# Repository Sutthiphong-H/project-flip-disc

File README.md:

# FlipDisc Project

FlipDisc Project was made for education of Project.
Chadsadakorn Piriyasiriphan
Jadesalit Suriyanimitsuk
Sutthiphong Hongkham

A webcam feed is segmented with RVM (Robust Video Matting; U2NET optional), each silhouette's distance is estimated from
its height, and everyone beyond `FLIPDISC_MAX_DISTANCE` is dropped. What's left is
reduced to an 80x45 black-and-white matrix and streamed to the React frontend over
Socket.IO. With nobody in range the backend loops an idle video instead.

## Layout

```
backend/
├── assets/            idle video clips
├── models/            model weights (not committed)
├── requirements.txt
├── src/
│   ├── app.py         entry point
│   ├── settings.py    every tunable, overridable by environment variable
│   ├── pipeline.py    capture -> segment -> publish loop
│   ├── frame_rate.py  rolling FPS meter
│   ├── sources/       webcam capture, idle video playback
│   ├── vision/        RVM + U2NET models, segmentation worker
│   └── server/        Flask + Socket.IO server and publisher
└── tools/camtest.py   preview a camera to find its index
flip-disc_frontend/    React client
arduino/               ESP32 sketches
```

## Installation

The RTX 50-series needs a CUDA 12.8 build of torch, so install torch first:

```bash
cd backend
pip install torch torchvision --index-url https://download.pytorch.org/whl/cu128
pip install -r requirements.txt
```

On a machine without an NVIDIA GPU, install the much smaller CPU build instead
(`--index-url https://download.pytorch.org/whl/cpu`). The backend runs on the CPU
by itself when there is no GPU, or the GPU fails a test run. That includes cards
older than the RTX 20-series, which the cu128 build has no kernels for. It also
falls back when the GPU can't load the model.

| Device | Model input | Per frame | fps with this webcam |
| ------ | ----------- | --------- | -------------------- |
| RTX 5060 (CUDA graph) | 1280x720 | ~8.5 ms | 20 (the camera's limit) |
| CPU, 6 threads | 640x360 | ~47 ms | ~17 |

The header of the page shows `GPU` or `CPU` (in amber) for the one in use.

Put the weights in `backend/models/`:

- `rvm_mobilenetv3.pth` -- the default model ([download](https://github.com/PeterL1n/RobustVideoMatting/releases/download/v1.0.0/rvm_mobilenetv3.pth))
- `u2net_human_seg.pth` -- only needed for `FLIPDISC_MODEL=u2net` ([download](https://drive.usercontent.google.com/download?id=1m_Kgs91b21gayc2XLW0ou8yugAIadWVP&export=download&authuser=0&confirm=t))

Put the idle clip at `backend/assets/video.mp4` (not in git -- it's 90 MB).

RVM's code in `backend/src/vision/rvm/` is vendored from [RobustVideoMatting](https://github.com/PeterL1n/RobustVideoMatting) and is GPL-3.0.

```bash
cd flip-disc_frontend
npm install
```

## Running

Build the frontend once and the backend serves it -- open http://localhost:5000:

```bash
cd flip-disc_frontend
npm run build            # -> flip-disc_frontend/dist (FLIPDISC_FRONTEND_DIST to move it)
cd ../backend
python src/app.py        # Flask + Socket.IO + the built page, all on port 5000
```

While working on the frontend, use Vite's dev server instead (http://localhost:5173,
talks to the backend on port 5000):

```bash
cd flip-disc_frontend
npm run dev
```

### Running unattended

`backend/run-backend.bat` runs the backend and restarts it whenever it exits with an
error. The backend exits with code 1 by itself when something breaks and won't
recover in place: the pipeline thread dies (a model that won't load, a CUDA context
broken by a GPU driver reset), segmentation hangs, or no frame goes out for
`FLIPDISC_STALL_SECONDS`. Frames go out in every mode (the idle clip plays even
without a camera), so a gap in them always means the backend is stuck. Ctrl+C exits with 0 and ends
the script too.

To start it with Windows, create a Task Scheduler task with the trigger **At log on**
and the action `backend\run-backend.bat`. Use log on rather than a Windows service:
services run outside the desktop session, and webcam access from there is unreliable. On the display machine, also turn off
sleep and USB selective suspend (Power Options → USB settings), or the webcam
can be powered down.

- `GET /status` returns 503 with `"status": "stalled"` once frames stop, for an
  external health check. Before the first frame the status is `"starting"`.
- The page shows *No frames from the backend* when it is connected but nothing has
  arrived for 3 s, and *Disconnected* once the backend has exited.
- If WebGL loses its context (a GPU reset, a driver update), the flip-disc view
  rebuilds itself. You don't need to reload.

Cameras are managed from the camera icon at the top right of the page: pick the
camera in use from the dropdown, and add, edit or delete cameras.

- **Webcam**: *Scan* shows the webcams plugged into the backend machine (with a
  thumbnail each); pick one, give it a name and a resolution.
- **IP camera**: name, IP, port, username, password, channel, main/sub stream,
  brand and resolution. The RTSP URL is built from those: Dahua
  `.../cam/realmonitor?channel=1&subtype=0` or Hikvision `.../Streaming/Channels/101`.
- *Test* grabs one frame and shows it. The backend only switches to a camera that
  delivers a picture, otherwise the current one keeps running.

The list lives in `backend/cameras.json` -- not committed, since it holds the IP
cameras' passwords, which the page never gets back (a blank password when editing
keeps the saved one). Without that file the backend starts with webcam `FLIPDISC_CAMERA`.

The page has three views: **Flip-disc** (the simulated display), **Mask** (the raw
80x45 matrix) and **Camera** (the webcam with the silhouette highlighted and a
distance box per person, streamed from `/debug.mjpg` only while it's open).

## Environment variables

| Variable                   | Default      | Meaning                                  |
| -------------------------- | ------------ | ---------------------------------------- |
| `FLIPDISC_CAMERA`          | `0`          | First webcam, until `cameras.json` exists |
| `FLIPDISC_PORT`            | `5000`       | Socket.IO / HTTP port                    |
| `FLIPDISC_EMIT_FPS`        | `30`         | Upper bound on frames sent to the client |
| `FLIPDISC_MAX_DISTANCE`    | `15`         | People further than this (m) are dropped |
| `FLIPDISC_FOCAL_LENGTH`    | `460`        | For the distance estimate; calibrate it  |
| `FLIPDISC_MIN_AREA`        | `0.005`      | Blobs under this share of frame = noise  |
| `FLIPDISC_MODEL`           | `rvm`        | `rvm` or `u2net`                         |
| `FLIPDISC_DEVICE`          | `auto`       | `auto`, `cuda` or `cpu`                  |
| `FLIPDISC_PROCESS_SIZE`    | per device   | Model input, 16:9. RVM: GPU 1280x720, CPU 640x360; U2NET 512x288 |
| `FLIPDISC_THIN_BOOST`      | `2`          | Extra weight for parts thinner than a disc (fingers); 0 = off |
| `FLIPDISC_SMOOTHING`       | `0.5`        | Anti-flicker; 1 = off, lower = steadier  |
| `FLIPDISC_IDLE_TIMEOUT`    | `15`         | Seconds without a person before idle     |
| `FLIPDISC_IDLE_VIDEO`      | `video.mp4`  | Clip in `backend/assets/` to loop        |
| `FLIPDISC_STALL_SECONDS`   | `10`         | No frame this long: exit for a restart   |
| `FLIPDISC_STARTUP_SECONDS` | `120`        | No first frame this long: same           |

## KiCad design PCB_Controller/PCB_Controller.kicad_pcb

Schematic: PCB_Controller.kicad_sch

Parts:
C1: 470uF/35V; CP_Radial_D10.0mm_P5.00mm
C2, C6, C9, C10, C11, C12, C13, C14, C15, C16, C17, C18, C19, C20, C21, C22, C23, C24, C25, C26, C27, C28, C29, C30, C31, C32, C33, C34, C35, C36, C37, C38, C39, C40: 0.1 uf; C_0805_2012Metric_Pad1.18x1.45mm_HandSolder
C3: 10uF/50V; C_1206_3216Metric_Pad1.33x1.80mm_HandSolder
C4: 22uF/10V; C_1206_3216Metric_Pad1.33x1.80mm_HandSolder
C8, C41, C43: 100nF; C_0805_2012Metric_Pad1.18x1.45mm_HandSolder
C42: 1000uF/35V; CP_Radial_D12.5mm_P5.00mm
D1: LED_Power_5V; LED_1206_3216Metric_Pad1.42x1.75mm_HandSolder
D2: SMBJ28CA; D_SMB
D3: 1N4744A; D_DO-41_SOD81_P7.62mm_Horizontal
F1: PPTC 3A; Fuse_Bourns_MF-RG300
J1: DC_Jack_5.5x2.5_24V; BarrelJack_CUI_PJ-063AH_Horizontal
J2: ColumnPin_1-12; IDC-Header_2x08_P2.54mm_Vertical
J3: ColumnPin_13-24; IDC-Header_2x08_P2.54mm_Vertical
J4: ColumnPin_25-36; IDC-Header_2x08_P2.54mm_Vertical
J5: RowPin_1-8; IDC-Header_2x08_P2.54mm_Vertical
J6: RowPin_9-16; IDC-Header_2x08_P2.54mm_Vertical
J7: RowPin17-24; IDC-Header_2x08_P2.54mm_Vertical
J8: Conn_01x05; PinHeader_1x05_P2.54mm_Vertical
J9: Screw_Terminal_24V; TerminalBlock_Phoenix_MKDS-1,5-2-5.08_1x02_P5.08mm_Horizont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
J10, J11: Conn_01x15; PinSocket_1x15_P2.54mm_Vertical
Q1: IRF4905; TO-220-3_Vertical
Q2, Q3, Q4, Q5, Q6, Q7, Q8, Q9: ULN2803APG_O,N,HZN; DIP-18_W7.62mm_Socket; Manufacturer_Part_Number ULN2803APG(O,N,HZN
R1: 2.2k; R_Axial_DIN0207_L6.3mm_D2.5mm_P7.62mm_Horizontal
R2, R3, R4, R5, R6, R7, R8, R9, R10, R11, R12, R13, R14, R15, R16, R17, R18, R19, R20, R21, R22, R23, R24, R25, R26, R27, R28, R29, R30, R31, R32, R33, R34, R35, R36, R37, R42, R43, R44, R45, R46, R47, R48, R49, R50, R51, R52, R53, R54, R55, R56, R57, R58, R59, R60, R61, R62, R63, R64, R65: 10k; R_Axial_DIN0207_L6.3mm_D2.5mm_P7.62mm_Horizontal
R38, R39, R41: 10k; R_0805_2012Metric_Pad1.20x1.40mm_HandSolder
R40: 47k; R_0805_2012Metric_Pad1.20x1.40mm_HandSolder
U1: TSR_1-2450; Converter_DCDC_TRACO_TSR-1_THT
U3: 74HC123; DIP-16_W7.62mm_Socket
U4: 74HCT245; DIP-20_W7.62mm_Socket
U5, U6, U7, U8, U9, U10, U11, U12, U13, U14, U25, U26, U27, U30, U31, U32: 74HC595; DIP-16_W7.62mm_Socket
U15, U16, U17, U18, U19, U33, U34, U35: UDN2981A; DIP-18_W7.62mm_Socket; MPN UDN2981A
U22: 74HC00; DIP-14_W7.62mm_Socket
U23: ESP32-DEVKIT-V1; MODULE_ESP32_DEVKIT_V1; PARTREV N/A

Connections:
+5V: C2.1, C4.1, C6.1, C9.1, C10.1, C11.1, C12.1, C13.2, C14.1, C15.1, C16.2, C27.2, C28.2, C32.2, C33.2, C34.2, C35.1, C36.1, C37.1, C41.1, C43.1, J8.2, J10.1, R1.1, R40.1, U1.3 (Vout), U3.16 (VCC), U4.1 (A->B), U4.20 (VCC), U5.16 (VCC), U6.16 (VCC), U7.16 (VCC), U8.16 (VCC), U9.16 (VCC), U10.16 (VCC), U11.16 (VCC), U12.16 (VCC), U13.16 (VCC), U14.16 (VCC), U22.14 (VCC), U23.30 (VIN), U25.16 (VCC), U26.16 (VCC), U27.16 (VCC), U30.16 (VCC), U31.16 (VCC), U32.16 (VCC)
+24V: C1.1, C3.1, C17.2, C18.2, C19.2, C20.2, C21.1, C22.2, C23.2, C24.2, C25.2, C26.1, C29.1, C30.1, C31.1, C38.1, C39.1, C40.2, C42.1, D3.1 (K), J8.3, Q1.3 (S), Q2.10 (COMMON), Q3.10 (COMMON), Q4.10 (COMMON), Q5.10 (COMMON), Q6.10 (COMMON), Q7.10 (COMMON), Q8.10 (COMMON), Q9.10 (COMMON), U1.1 (Vin), U15.9 (VS), U16.9 (VS), U17.9 (VS), U18.9 (VS), U19.9 (VS), U33.9 (VS), U34.9 (VS), U35.9 (VS)
/Clear: J10.6, U4.6 (A4), U23.25 (D27)
/Clear_5V: U4.14 (B4), U5.10 (~SRCLR), U6.10 (~SRCLR), U7.10 (~SRCLR), U8.10 (~SRCLR), U9.10 (~SRCLR), U10.10 (~SRCLR), U11.10 (~SRCLR), U12.10 (~SRCLR), U13.10 (~SRCLR), U14.10 (~SRCLR), U25.10 (~SRCLR), U26.10 (~SRCLR), U27.10 (~SRCLR), U30.10 (~SRCLR), U31.10 (~SRCLR), U32.10 (~SRCLR)
/Clock: J11.9, U4.3 (A1), U23.9 (D18)
/Clock_5V: U4.17 (B1), U5.11 (SRCLK), U6.11 (SRCLK), U7.11 (SRCLK), U8.11 (SRCLK), U9.11 (SRCLK), U10.11 (SRCLK), U11.11 (SRCLK), U12.11 (SRCLK), U13.11 (SRCLK), U14.11 (SRCLK), U25.11 (SRCLK), U26.11 (SRCLK), U27.11 (SRCLK), U30.11 (SRCLK), U31.11 (SRCLK), U32.11 (SRCLK)
/Column_Latch: J10.8, U4.4 (A2), U23.23 (D25)
/Column_Latch_5V: U4.16 (B2), U5.12 (RCLK), U6.12 (RCLK), U7.12 (RCLK), U8.12 (RCLK), U9.12 (RCLK), U10.12 (RCLK), U11.12 (RCLK), U12.12 (RCLK), U13.12 (RCLK), U14.12 (RCLK)
/D2: J11.4, U23.4 (D2)
/D4: J11.5, U23.5 (D4)
/D5: J11.8, U23.8 (D5)
/D12: J10.4, U23.27 (D12)
/D13: J10.3, U23.28 (D13)
/D14: J10.5, U23.26 (D14)
/D15: J11.3, U23.3 (D15)
/D19: J11.10, U23.10 (D19)
/D21: J11.11, U23.11 (D21)
/D22: J11.14, U23.14 (D22)
/D34: J10.12, U23.19 (D34)
/D35: J10.11, U23.20 (D35)
/Data: J11.15, U4.2 (A0), U23.15 (D23)
/Data_5V: U4.18 (B0), U9.14 (SER), U14.14 (SER), U27.14 (SER), U32.14 (SER)
/EN: J10.15, U23.16 (EN)
/ESP_3V3: J8.1, J11.1, U23.1 (3V3)
/MONO_C: C8.2, U3.14 (Cext)
/MONO_RC: C8.1, R40.2, U3.15 (RCext)
/Pulse: J10.10, R38.1, U4.7 (A5), U23.21 (D32)
/Pulse_5V: U3.2 (B), U3.3 (Clr), U4.13 (B5)
/Pulse_Gated: U3.13 (Q), U22.2, U22.5
/Q1_GATE: D3.2 (A), Q1.1 (G), R41.1
/RX0: J11.12, U23.12 (RX0)
/RX2: J11.6, U23.6 (RX2)
/Row_Latch: J10.7, U4.5 (A3), U23.24 (D26)
/Row_Latch_5V: U4.15 (B3), U25.12 (RCLK), U26.12 (RCLK), U27.12 (RCLK), U30.12 (RCLK), U31.12 (RCLK), U32.12 (RCLK)
/SR_N: U10.13 (~OE), U11.13 (~OE), U12.13 (~OE), U13.13 (~OE), U14.13 (~OE), U22.4, U22.8
/Set_Reset: J10.9, R39.1, U4.8 (A6), U23.22 (D33)
/Set_Reset_5V: U4.12 (B6), U22.1, U22.9, U22.10
/TX0: J11.13, U23.13 (TX0)
/TX2: J11.7, U23.7 (TX2)
/VIN_FUSED: D2.1 (A1), F1.2, Q1.2 (D)
/VIN_RAW: F1.1, J1.1, J9.1
/VN: J10.13, U23.18 (VN)
/VP: J10.14, U23.17 (VP)
Col1: J2.1, Q6.18 (O1), U19.18 (OUT1)
Col2: J2.2, Q6.17 (O2), U19.17 (OUT2)
Col3: J2.3, Q6.16 (O3), U19.16 (OUT3)
Col4: J2.4, Q6.15 (O4), U19.15 (OUT4)
Col5: J2.5, Q6.14 (O5), U19.14 (OUT5)
Col6: J2.6, Q6.13 (O6), U19.13 (OUT6)
Col7: J2.7, Q6.12 (O7), U19.12 (OUT7)
Col8: J2.8, Q6.11 (O8), U19.11 (OUT8)
Col9: J2.9, Q5.18 (O1), U18.18 (OUT1)
Col10: J2.10, Q5.17 (O2), U18.17 (OUT2)
Col11: J2.11, Q5.16 (O3), U18.16 (OUT3)
Col12: J2.12, Q5.15 (O4), U18.15 (OUT4)
Col13: J3.1, Q5.14 (O5), U18.14 (OUT5)
Col14: J3.2, Q5.13 (O6), U18.13 (OUT6)
Col15: J3.3, Q5.12 (O7), U18.12 (OUT7)
Col16: J3.4, Q5.11 (O8), U18.11 (OUT8)
Col17: J3.5, Q4.18 (O1), U17.18 (OUT1)
Col18: J3.6, Q4.17 (O2), U17.17 (OUT2)
Col19: J3.7, Q4.16 (O3), U17.16 (OUT3)
Col20: J3.8, Q4.15 (O4), U17.15 (OUT4)
Col21: J3.9, Q4.14 (O5), U17.14 (OUT5)
Col22: J3.10, Q4.13 (O6), U17.13 (OUT6)
Col23: J3.11, Q4.12 (O7), U17.12 (OUT7)
Col24: J3.12, Q4.11 (O8), U17.11 (OUT8)
Col25: J4.1, Q3.18 (O1), U16.18 (OUT1)
Col26: J4.2, Q3.17 (O2), U16.17 (OUT2)
Col27: J4.3, Q3.16 (O3), U16.16 (OUT3)
Col28: J4.4, Q3.15 (O4), U16.15 (OUT4)
Col29: J4.5, Q3.14 (O5), U16.14 (OUT5)
Col30: J4.6, Q3.13 (O6), U16.13 (OUT6)
Col31: J4.7, Q3.12 (O7), U16.12 (OUT7)
Col32: J4.8, Q3.11 (O8), U16.11 (OUT8)
Col33: J4.9, Q2.18 (O1), U15.18 (OUT1)
Col34: J4.10, Q2.17 (O2), U15.17 (OUT2)
Col35: J4.11, Q2.16 (O3), U15.16 (OUT3)
Col36: J4.12, Q2.15 (O4), U15.15 (OUT4)
GND1: C1.2, C2.2, C3.2, C4.2, C6.2, C9.2, C10.2, C11.2, C12.2, C13.1, C14.2, C15.2, C16.1, C17.1, C18.1, C19.1, C20.1, C21.2, C22.1, C23.1, C24.1, C25.1, C26.2, C27.1, C28.1, C29.2, C30.2, C31.2, C32.1, C33.1, C34.1, C35.2, C36.2, C37.2, C38.2, C39.2, C40.1, C41.2, C42.2, C43.2, D1.1 (K), D2.2 (A2), J1.2, J8.4, J8.5, J9.2, J10.2, J11.2, Q2.9 (GND), Q3.9 (GND), Q4.9 (GND), Q5.9 (GND), Q6.9 (GND), Q7.9 (GND), Q8.9 (GND), Q9.9 (GND), R2.2, R3.2, R4.2, R5.2, R6.2, R7.2, R8.2, R9.2, R10.2, R11.2, R12.2, R13.2, R14.2, R15.2, R16.2, R17.2, R18.2, R19.2, R20.2, R21.2, R22.2, R23.2, R24.2, R25.2, R26.2, R27.2, R28.2, R29.2, R30.2, R31.2, R32.2, R33.2, R34.1, R35.1, R36.1, R37.1, R38.2, R39.2, R41.2, R42.2, R43.2, R44.2, R45.2, R46.2, R47.2, R48.2, R49.2, R50.2, R51.2, R52.2, R53.2, R54.2, R55.2, R56.2, R57.2, R58.2, R59.2, R60.2, R61.2, R62.2, R63.2, R64.2, R65.2, U1.2 (GND), U3.1 (A), U3.8 (GND), U3.9 (A), U3.10 (B), U3.11 (Clr), U4.9 (A7), U4.10 (GND), U4.19 (CE), U5.8 (GND), U6.8 (GND), U7.8 (GND), U8.8 (GND), U9.8 (GND), U10.8 (GND), U11.8 (GND), U12.8 (GND), U13.8 (GND), U14.8 (GND), U15.10 (GND), U16.10 (GND), U17.10 (GND), U18.10 (GND), U19.10 (GND), U22.7 (GND), U23.2 (GND), U23.29 (GND), U25.8 (GND), U26.8 (GND), U27.8 (GND), U30.8 (GND), U31.8 (GND), U32.8 (GND), U33.10 (GND), U34.10 (GND), U35.10 (GND)
unnamed: D1.2 (A), R1.2
unnamed: Q2.1 (I1), U10.15 (QA)
unnamed: Q2.2 (I2), U10.1 (QB)
unnamed: Q2.3 (I3), U10.2 (QC)
unnamed: Q2.4 (I4), U10.3 (QD)
unnamed: Q3.1 (I1), U11.15 (QA)
unnamed: Q3.2 (I2), U11.1 (QB)
unnamed: Q3.3 (I3), U11.2 (QC)
unnamed: Q3.4 (I4), U11.3 (QD)
unnamed: Q3.5 (I5), U11.4 (QE)
unnamed: Q3.6 (I6), U11.5 (QF)
unnamed: Q3.7 (I7), U11.6 (QG)
unnamed: Q3.8 (I8), U11.7 (QH)
unnamed: Q4.1 (I1), U12.15 (QA)
unnamed: Q4.2 (I2), U12.1 (QB)
unnamed: Q4.3 (I3), U12.2 (QC)
unnamed: Q4.4 (I4), U12.3 (QD)
unnamed: Q4.5 (I5), U12.4 (QE)
unnamed: Q4.6 (I6), U12.5 (QF)
unnamed: Q4.7 (I7), U12.6 (QG)
unnamed: Q4.8 (I8), U12.7 (QH)
unnamed: Q5.1 (I1), U13.15 (QA)
unnamed: Q5.2 (I2), U13.1 (QB)
unnamed: Q5.3 (I3), U13.2 (QC)
unnamed: Q5.4 (I4), U13.3 (QD)
unnamed: Q5.5 (I5), U13.4 (QE)
unnamed: Q5.6 (I6), U13.5 (QF)
unnamed: Q5.7 (I7), U13.6 (QG)
unnamed: Q5.8 (I8), U13.7 (QH)
unnamed: Q6.1 (I1), U14.15 (QA)
unnamed: Q6.2 (I2), U14.1 (QB)
unnamed: Q6.3 (I3), U14.2 (QC)
unnamed: Q6.4 (I4), U14.3 (QD)
unnamed: Q6.5 (I5), U14.4 (QE)
unnamed: Q6.6 (I6), U14.5 (QF)
unnamed: Q6.7 (I7), U14.6 (QG)
unnamed: Q6.8 (I8), U14.7 (QH)
unnamed: Q7.1 (I1), U32.15 (QA)
unnamed: Q7.2 (I2), U32.1 (QB)
unnamed: Q7.3 (I3), U32.2 (QC)
unnamed: Q7.4 (I4), U32.3 (QD)
unnamed: Q7.5 (I5), U32.4 (QE)
unnamed: Q7.6 (I6), U32.5 (QF)
unnamed: Q7.7 (I7), U32.6 (QG)
unnamed: Q7.8 (I8), U32.7 (QH)
unnamed: Q8.1 (I1), U31.15 (QA)
unnamed: Q8.2 (I2), U31.1 (QB)
unnamed: Q8.3 (I3), U31.2 (QC)
unnamed: Q8.4 (I4), U31.3 (QD)
unnamed: Q8.5 (I5), U31.4 (QE)
unnamed: Q8.6 (I6), U31.5 (QF)
unnamed: Q8.7 (I7), U31.6 (QG)
unnamed: Q8.8 (I8), U31.7 (QH)
unnamed: Q9.1 (I1), U30.15 (QA)
unnamed: Q9.2 (I2), U30.1 (QB)
unnamed: Q9.3 (I3), U30.2 (QC)
unnamed: Q9.4 (I4), U30.3 (QD)
unnamed: Q9.5 (I5), U30.4 (QE)
unnamed: Q9.6 (I6), U30.5 (QF)
unnamed: Q9.7 (I7), U30.6 (QG)
unnamed: Q9.8 (I8), U30.7 (QH)
unnamed: U5.14 (SER), U6.9 (QH')
unnamed: U6.14 (SER), U7.9 (QH')
unnamed: U7.14 (SER), U8.9 (QH')
unnamed: U8.14 (SER), U9.9 (QH')
unnamed: U10.14 (SER), U11.9 (QH')
unnamed: U11.14 (SER), U12.9 (QH')
unnamed: U12.14 (SER), U13.9 (QH')
unnamed: U13.14 (SER), U14.9 (QH')
unnamed: R34.2, U5.15 (QA), U15.1 (IN1)
unnamed: R35.2, U5.1 (QB), U15.2 (IN2)
unnamed: R36.2, U5.2 (QC), U15.3 (IN3)
unnamed: R37.2, U5.3 (QD), U15.4 (IN4)
unnamed: R33.1, U6.15 (QA), U16.1 (IN1)
unnamed: R32.1, U6.1 (QB), U16.2 (IN2)
unnamed: R31.1, U6.2 (QC), U16.3 (IN3)
unnamed: R30.1, U6.3 (QD), U16.4 (IN4)
unnamed: R29.1, U6.4 (QE), U16.5 (IN5)
unnamed: R28.1, U6.5 (QF), U16.6 (IN6)
unnamed: R27.1, U6.6 (QG), U16.7 (IN7)
unnamed: R26.1, U6.7 (QH), U16.8 (IN8)
unnamed: R25.1, U7.15 (QA), U17.1 (IN1)
unnamed: R24.1, U7.1 (QB), U17.2 (IN2)
unnamed: R23.1, U7.2 (QC), U17.3 (IN3)
unnamed: R22.1, U7.3 (QD), U17.4 (IN4)
unnamed: R21.1, U7.4 (QE), U17.5 (IN5)
unnamed: R20.1, U7.5 (QF), U17.6 (IN6)
unnamed: R19.1, U7.6 (QG), U17.7 (IN7)
unnamed: R18.1, U7.7 (QH), U17.8 (IN8)
unnamed: R17.1, U8.15 (QA), U18.1 (IN1)
unnamed: R16.1, U8.1 (QB), U18.2 (IN2)
unnamed: R15.1, U8.2 (QC), U18.3 (IN3)
unnamed: R14.1, U8.3 (QD), U18.4 (IN4)
unnamed: R13.1, U8.4 (QE), U18.5 (IN5)
unnamed: R12.1, U8.5 (QF), U18.6 (IN6)
unnamed: R11.1, U8.6 (QG), U18.7 (IN7)
unnamed: R10.1, U8.7 (QH), U18.8 (IN8)
unnamed: R9.1, U9.15 (QA), U19.1 (IN1)
unnamed: R8.1, U9.1 (QB), U19.2 (IN2)
unnamed: R7.1, U9.2 (QC), U19.3 (IN3)
unnamed: R6.1, U9.3 (QD), U19.4 (IN4)
unnamed: R5.1, U9.4 (QE), U19.5 (IN5)
unnamed: R4.1, U9.5 (QF), U19.6 (IN6)
unnamed: R3.1, U9.6 (QG), U19.7 (IN7)
unnamed: R2.1, U9.7 (QH), U19.8 (IN8)
unnamed: R58.1, U25.15 (QA), U35.1 (IN1)
unnamed: R59.1, U25.1 (QB), U35.2 (IN2)
unnamed: R60.1, U25.2 (QC), U35.3 (IN3)
unnamed: R61.1, U25.3 (QD), U35.4 (IN4)
unnamed: R62.1, U25.4 (QE), U35.5 (IN5)
unnamed: R63.1, U25.5 (QF), U35.6 (IN6)
unnamed: R64.1, U25.6 (QG), U35.7 (IN7)
unnamed: R65.1, U25.7 (QH), U35.8 (IN8)
unnamed: U25.14 (SER), U26.9 (QH')
unnamed: U22.3, U25.13 (~OE), U26.13 (~OE), U27.13 (~OE)
unnamed: R50.1, U26.15 (QA), U34.1 (IN1)
unnamed: R51.1, U26.1 (QB), U34.2 (IN2)
unnamed: R52.1, U26.2 (QC), U34.3 (IN3)
unnamed: R53.1, U26.3 (QD), U34.4 (IN4)
unnamed: R54.1, U26.4 (QE), U34.5 (IN5)
unnamed: R55.1, U26.5 (QF), U34.6 (IN6)
unnamed: R56.1, U26.6 (QG), U34.7 (IN7)
unnamed: R57.1, U26.7 (QH), U34.8 (IN8)
unnamed: U26.14 (SER), U27.9 (QH')
unnamed: R42.1, U27.15 (QA), U33.1 (IN1)
unnamed: R43.1, U27.1 (QB), U33.2 (IN2)
unnamed: R44.1, U27.2 (QC), U33.3 (IN3)
unnamed: R45.1, U27.3 (QD), U33.4 (IN4)
unnamed: R46.1, U27.4 (QE), U33.5 (IN5)
unnamed: R47.1, U27.5 (QF), U33.6 (IN6)
unnamed: R48.1, U27.6 (QG), U33.7 (IN7)
unnamed: R49.1, U27.7 (QH), U33.8 (IN8)
unnamed: U30.14 (SER), U31.9 (QH')
unnamed: U5.13 (~OE), U6.13 (~OE), U7.13 (~OE), U8.13 (~OE), U9.13 (~OE), U22.6, U30.13 (~OE), U31.13 (~OE), U32.13 (~OE)
unnamed: U31.14 (SER), U32.9 (QH')
Row 1 +: J5.2, U33.18 (OUT1)
Row 1 -: J5.1, Q7.18 (O1)
Row 2 +: J5.4, U33.17 (OUT2)
Row 2 -: J5.3, Q7.17 (O2)
Row 3 +: J5.6, U33.16 (OUT3)
Row 3 -: J5.5, Q7.16 (O3)
Row 4 +: J5.8, U33.15 (OUT4)
Row 4 -: J5.7, Q7.15 (O4)
Row 5 +: J5.10, U33.14 (OUT5)
Row 5 -: J5.9, Q7.14 (O5)
Row 6 +: J5.12, U33.13 (OUT6)
Row 6 -: J5.11, Q7.13 (O6)
Row 7 +: J5.14, U33.12 (OUT7)
Row 7 -: J5.13, Q7.12 (O7)
Row 8 +: J5.16, U33.11 (OUT8)
Row 8 -: J5.15, Q7.11 (O8)
Row 9 +: J6.2, U34.18 (OUT1)
Row 9 -: J6.1, Q8.18 (O1)
Row 10 +: J6.4, U34.17 (OUT2)
Row 10 -: J6.3, Q8.17 (O2)
Row 11 +: J6.6, U34.16 (OUT3)
Row 11 -: J6.5, Q8.16 (O3)
Row 12 +: J6.8, U34.15 (OUT4)
Row 12 -: J6.7, Q8.15 (O4)
Row 13 +: J6.10, U34.14 (OUT5)
Row 13 -: J6.9, Q8.14 (O5)
Row 14 +: J6.12, U34.13 (OUT6)
Row 14 -: J6.11, Q8.13 (O6)
Row 15 +: J6.14, U34.12 (OUT7)
Row 15 -: J6.13, Q8.12 (O7)
Row 16 +: J6.16, U34.11 (OUT8)
Row 16 -: J6.15, Q8.11 (O8)
Row 17 +: J7.2, U35.18 (OUT1)
Row 17 -: J7.1, Q9.18 (O1)
Row 18 +: J7.4, U35.17 (OUT2)
Row 18 -: J7.3, Q9.17 (O2)
Row 19 +: J7.6, U35.16 (OUT3)
Row 19 -: J7.5, Q9.16 (O3)
Row 20 +: J7.8, U35.15 (OUT4)
Row 20 -: J7.7, Q9.15 (O4)
Row 21 +: J7.10, U35.14 (OUT5)
Row 21 -: J7.9, Q9.14 (O5)
Row 22 +: J7.12, U35.13 (OUT6)
Row 22 -: J7.11, Q9.13 (O6)
Row 23 +: J7.14, U35.12 (OUT7)
Row 23 -: J7.13, Q9.12 (O7)
Row 24 +: J7.16, U35.11 (OUT8)
Row 24 -: J7.15, Q9.11 (O8)

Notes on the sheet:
FlipFlop
Pins
PSU_Status_OK
Power Out pin
Row_Source
Data
Power Organize
Flipdisc_Display Controller
Power Source
Column_Source
reset_pulse
Set_pulse
Row_Sink
Column_Sink
J2-J7: 2x8 IDC box header (HUB75-style). Pin N = old header pin N. Carries 12V flip-disc coil drive - NOT for HUB75 LED panels!

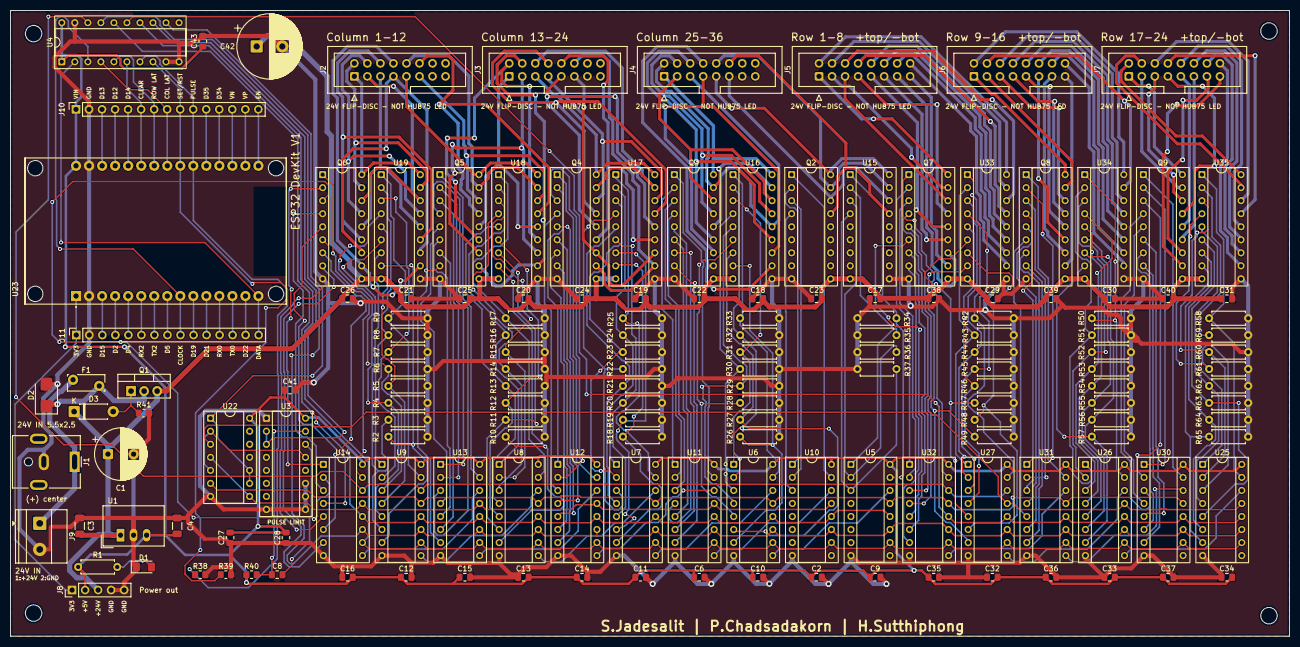
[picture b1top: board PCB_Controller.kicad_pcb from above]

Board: 2 copper layers, 249.4 x 122.0 mm, 159 parts (0 on the bottom side), 263 nets.
